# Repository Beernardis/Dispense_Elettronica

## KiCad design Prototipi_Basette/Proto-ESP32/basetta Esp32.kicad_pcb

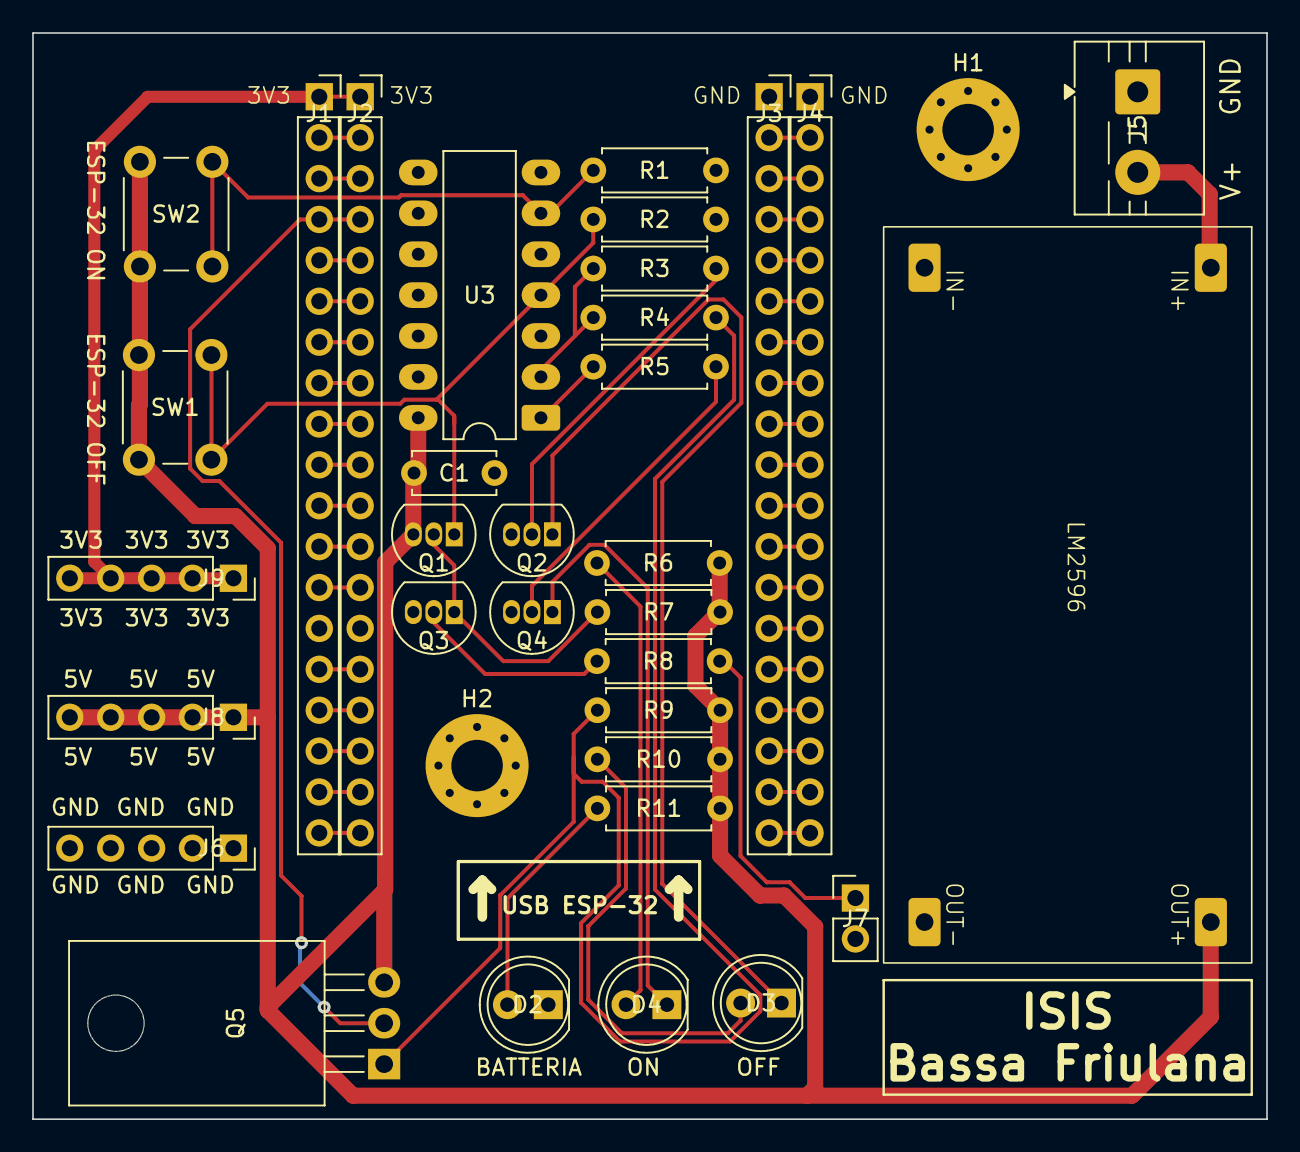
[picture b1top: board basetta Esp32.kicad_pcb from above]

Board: 2 copper layers, 76.6 x 67.5 mm, 35 parts (0 on the bottom side), 54 nets.

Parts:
C1: 100n; C_Disc_D5.0mm_W2.5mm_P5.00mm
D2: LED; LED_D5.0mm
D3: ESP32 OFF; LED_D5.0mm
D4: ESP32 ON; LED_D5.0mm
H1, H2: MountingHole_Pad; MountingHole_3.2mm_M3_Pad_Via
J1, J2, J3, J4: Conn_01x19; PinSocket_1x19_P2.54mm_Vertical
J5: Screw_Terminal_01x02; TerminalBlock_MaiXu_MX126-5.0-02P_1x02_P5.00mm
J6, J8, J9: Conn_01x05; PinSocket_1x05_P2.54mm_Vertical
J7: Conn_01x02; PinHeader_1x02_P2.54mm_Vertical
LM2596: LM2596 - IC
Q1: BC557; TO-92_Inline
Q2, Q3, Q4: BC547; TO-92_Inline
Q5: IRF9540N; TO-220-3_Horizontal_TabDown
R1, R2, R9: 10k; R_Axial_DIN0207_L6.3mm_D2.5mm_P7.62mm_Horizontal
R3, R5: 4.7 k; R_Axial_DIN0207_L6.3mm_D2.5mm_P7.62mm_Horizontal
R4, R6, R10: 470; R_Axial_DIN0207_L6.3mm_D2.5mm_P7.62mm_Horizontal
R7: R; R_Axial_DIN0207_L6.3mm_D2.5mm_P7.62mm_Horizontal
R8: 2.2k; R_Axial_DIN0207_L6.3mm_D2.5mm_P7.62mm_Horizontal
R11: 1k; R_Axial_DIN0207_L6.3mm_D2.5mm_P7.62mm_Horizontal
SW1: RESET; SW_PUSH_6mm_H4.3mm
SW2: SET; SW_PUSH_6mm_H4.3mm
U3: 4013; DIP-14_W7.62mm_LongPads

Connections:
+3V3: J1.1, J2.1, J9.1, J9.2, J9.3, J9.4, J9.5
+5V: C1.1, J8.1, J8.2, J8.3, J8.4, J8.5, LM2596.3 (OUT+), Q1.3 (E), Q5.3 (S), R6.1, R7.1, R9.2, R10.1, R11.1, SW1.1, SW2.1, U3.14 (VDD)
ESP-32 POW: J1.4, J2.4, Q5.2 (D)
GND: C1.2, D2.1 (K), H1.1 (1_1), H2.1 (1_1), J1.14, J2.14, J3.1, J4.1, J5.1, J6.1, J6.2, J6.3, J6.4, J6.5, J7.2, LM2596.2 (IN-), LM2596.4 (OUT-), Q2.3 (E), Q3.3 (E), Q4.3 (E), R1.2, R2.2, U3.3 (C), U3.5 (D), U3.7 (VSS), U3.8 (S), U3.9 (D), U3.10 (R), U3.11 (C)
unnamed: D2.2 (A), R11.2
unnamed: D3.2 (A), R10.2
unnamed: D3.1 (K), Q2.1 (C)
unnamed: D4.2 (A), R6.2
unnamed: D4.1 (K), Q4.1 (C)
unnamed: J1.2, J2.2
unnamed: J1.3, J2.3
unnamed: J1.5, J2.5
unnamed: J1.6, J2.6
unnamed: J1.7, J2.7
unnamed: J1.8, J2.8
unnamed: J1.9, J2.9
unnamed: J1.10, J2.10
unnamed: J1.11, J2.11
unnamed: J1.12, J2.12
unnamed: J1.13, J2.13
unnamed: J1.15, J2.15
unnamed: J1.16, J2.16
unnamed: J1.17, J2.17
unnamed: J1.18, J2.18
unnamed: J1.19, J2.19
unnamed: J3.2, J4.2
unnamed: J3.3, J4.3
unnamed: J3.4, J4.4
unnamed: J3.5, J4.5
unnamed: J3.6, J4.6
unnamed: J3.7, J4.7
unnamed: J3.8, J4.8
unnamed: J3.9, J4.9
unnamed: J3.10, J4.10
unnamed: J3.11, J4.11
unnamed: J3.12, J4.12
unnamed: J3.13, J4.13
unnamed: J3.14, J4.14
unnamed: J3.15, J4.15
unnamed: J3.16, J4.16
unnamed: J3.17, J4.17
unnamed: J3.18, J4.18
unnamed: J3.19, J4.19
unnamed: J7.1, R8.1
unnamed: Q1.2 (B), Q3.1 (C), R7.2
unnamed: Q2.2 (B), R3.2
unnamed: Q3.2 (B), R8.2
unnamed: Q4.2 (B), R5.2
unnamed: Q5.1 (G), R4.2, R9.1
unnamed: R5.1, U3.1 (Q)
unnamed: R1.1, SW2.2, U3.6 (S)
SIGN_ESP32: R3.1, R4.1, U3.2 (~Q)
Suicide: Q1.1 (C), R2.1, SW1.2, U3.4 (R)
V_in_Batterie: J5.2, LM2596.1 (IN+)

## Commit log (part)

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2026-03-15 Primo commit
2026-03-16 Add Sarrus diagram and adjust TikZ config
    Introduce a TikZ illustration of Sarrus' rule in Gauss_Jordan.tex and clarify the explanatory text (explicitly mention the 3x5 layout and diagonal conventions). Reformat determinant calculations for 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
2026-03-17 Add Metodo Correnti di Maglia chapter & exercises
    Introduce the 'Metodo delle Correnti di Maglia' content: add CorrentiMaglia.tex (chapter) and a comprehensive Esercizi.tex with exercise sets and worked solutions (Cramer's rule and Gauss–Jordan). Re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
2026-03-17 Restructure methods and add DC & Sallen-Key drafts
    Reorganize and expand course material: rename MetodoPotenzialeNodi to Metodi_AC (capitolo1/2 and main.tex). Add a new Metodi_DC module with chapters for Correnti_Maglia, Potenziale_Nodi, PDSDE (super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
2026-03-18 Rename Metodi_DC files and add mesh chapter
    Reorganize MetodiRisolutiviReti/Metodi_DC: add a new numbered chapter file 1_Correnti_Maglia.tex (detailed mesh-current method with circuit example), delete the old Correnti_Maglia.tex, and rename ex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
2026-03-18 Revise mesh-current example and add procedure
    Reworks the 'correnti di maglia' example: minor wording cleanup in the mesh-current definition, adds a systematic step-by-step procedure to derive mesh equations, and introduces a more detailed circu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
2026-03-18 Enhance mesh-current method section
    Add detailed exposition of the mesh-current (correnti di maglia) method: introductory paragraph on its purpose, requirements for planar circuits, and identification of independent meshes. Clarify Eul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
2026-03-18 Refine mesh-current example and add matrix section
    Improve formatting and pedagogy of the mesh-current example: enlarge the example subsection title, add horizontal rules for visual separation, and tweak enumeration labels (rename steps and make the 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
2026-03-19 Aggiungi vettore corrente di maglia e vettore b
    Aggiunte le sottosezioni che definiscono il vettore incognita I e il vettore dei termini noti b, con convenzione sui segni per i generatori. Inseriti esempi espliciti di I e b, la forma matriciale es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
2026-03-19 Gestione generatori di corrente nel metodo maglie
    Aggiunta una sezione che tratta il problema dei generatori di corrente nel metodo delle correnti di maglia. Introduce la procedura: mantenere le correnti di maglia come incognite, aggiungere variabil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
2026-03-19 Terminato Correnti di maglia
    Non compila, probabilmente problemi di include/input
2026-03-20 Update mesh-current chapter: edits & fixes
    Replace \include with \input and perform multiple content and formatting refinements in the mesh-current (correnti di maglia) chapter. Expanded and clarified the procedural steps (LKT, Ohm, matrix fo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
2026-03-20 Restructure DC methods and add node method
    Reorganize Metodi_DC layout and add the Metodo del potenziale ai nodi chapter. Several files were moved/renamed into per-chapter subfolders (3,4,5,6 renamed to their /<n>_main.tex paths). Removed obs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
2026-03-21 Enhance node-potential docs and circuit macros
    Refine documentation and diagram macros for the nodal-potential method:
    - Risoluzione_E.tex: rename section from "Procedura di risoluzione" to "Problema del generatore di tensione".
    - Risoluzione_J.tex: replace placeholder with a full step-by-step nodal-potential procedure, including theory, example, KCL equations, Ohm-law substitutions and matrix form; adds explanatory figures 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
    - cenni_teorici.tex: small wording/formatting fixes around Ohm's law and conductances.
    - Circuiti.tex: overhaul the \CircuitoPotenzialeNodi macro to draw explicit current/voltage sources, support grounded and non-grounded variants, i
2026-03-22 Metodo dei nodi: generatori di tensione
    Aggiunge una sezione completa che spiega come gestire generatori di tensione ideali nel metodo dei potenziali ai nodi: vengono introdotte le correnti dei generatori come incognite, le equazioni di vi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
2026-03-23 Fix nodal equations and correct source labels
    Correct KCL equations and expand the nodal analysis in Resoluzione_E.tex: clarify current directions for voltage sources, rename nodes consistently (A, C, D), rewrite KCLs, apply Ohm's law using cond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
2026-03-23 Include voltage source currents in node KCL
    Refactor the node KCL/Ohm section to explicitly include the unknown currents of voltage sources (I_{E1}, I_{E2}) and update the corresponding KCL equations and Ohm-law substitutions. Replace itemize 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
2026-03-24 Fix voltage-source constraints and matrix signs
    Clarify and correct the voltage-source connections and their algebraic constraints: E1 is now defined between D and C and E2 between A and B (previously C–D and B–C). The source equations were rewrit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
2026-03-27 Refactor LaTeX: move documentclass, adjust macros
    Centralize document class and tidy LaTeX sources: moved \documentclass from MetodiRisolutiviReti/Metodi_DC/_main.tex into config/config.tex (now \documentclass[a4paper, 11pt]{book}). Update header to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
2026-03-27 Add LaTeX main and update config
    Create a top-level LaTeX entry point (LaTeX/main.tex) with title, TOC and several chapter placeholders. Remove the duplicate \documentclass from config/config.tex and centralize package setup by addi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
2026-03-29 Use identity block for voltage sources and update matrix
    Replace the bottom-right zero block in the augmented nodal matrix with an identity to represent independent voltage-source currents. Update the E and I block definitions and the expanded 5x5 system r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
2026-03-31 Fix node labels and sign in nodal equations
    Rename ZoomNodo references for nodes A, C and D to A_1, C_1, D_1 and add matching drawing cases in Circuiti.tex for the new zoom identifiers. Correct the sign of the J_2 term in node D's KCL and upda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
2026-04-01 Add Arduino LED tutorial (Italian LaTeX)
    Add new LaTeX file Arduino/main.tex containing a comprehensive Italian chapter on LEDs. Covers physical principles, polarity, electrical parameters, resistor calculation, breadboard wiring, PWM, and 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
2026-04-01 Extract LED chapter to Arduino/LED.tex
    Move the LED chapter out of main.tex into a new Arduino/LED.tex to modularize the documentation. Added accompanying images (Arduino/img/Circuito_LED_Generatore.png and Arduino/img/Struttura_fisica_LE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
2026-04-01 Add LED PWM example and formatting tweaks
    Introduce a new Arduino example (Esempio 2) demonstrating PWM-driven LED brightness using analogWrite on PIN_LED = 13 with two duty cycles (50 and 200) and 1s delays. Also add horizontal rules around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
2026-04-03 Add LED circuit images and examples
    Insert two new circuit images and a side-by-side figure into Arduino/LED.tex to illustrate a 5V test circuit and an Arduino-driven LED circuit. Update explanatory text to reference the new figures, u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
2026-04-03 Update LED chapter: formatting, examples, RGB
    Refactor LED chapter: convert many \subsection to unnumbered \subsection*, adjust figure layout (minipage widths and image sizing) and captions, and tweak math/notation for clarity. Add a new "LED RG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
2026-04-04 Update LED chapter: PWM, RGB, examples
    Revise LED chapter: refactor sections and examples for clarity and PWM/RGB usage. Made subsection unnumbered, adjusted image sizing, replaced circuitikz diagram with raster image, and updated recomme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
2026-04-08 Add Arduino board sheet and pinout image
    Add new Schede_Arduino.tex and Arduino_uno_PinOut.jpg to provide an Arduino board sheet/pinout reference, and update main.tex to include the new Schede_Arduino file so the pinout is included in the c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
2026-04-08 Add Arduino chapter file
    Add new LaTeX chapter file Arduino/Schede_Arduino.tex containing a chapter header '\chapter{Scheda Arduino}' as a placeholder for Arduino content.
2026-04-09 Expand Arduino chapter with intro and pin details
    Replace the old 'Scheda Arduino' chapter with a much more detailed 'Introduzione ad Arduino'. Adds structured sections on the Arduino Uno overview, power (USB, DC jack, Vin), onboard linear regulator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
2026-04-28 Add Pulsante chapter and button images
    Add a new Arduino chapter (pulsante.tex) documenting push-button usage: structure, pull-up/pull-down wiring, internal pull-up, debouncing (software delay and Bounce2), press-duration measurement, and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
2026-05-01 Document serial TX/RX and add Bounce2 example
    Adds a new detailed section about serial communication (USART/UART) to Schede_Arduino.tex covering pins 0/1 (RX/TX), baud rate, USB-serial converter (ATmega16U2), TX/RX LEDs and upload-time interfere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
2026-05-11 Add ESP32 prototype PCB and backup files
    Import KiCad project for basetta Esp32 including basetta Esp32.kicad_pcb, .kicad_sch, .kicad_pro, .kicad_prl and fp-info-cache, plus multiple timestamped backup ZIPs under Prototipi Basette/Proto-ESP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
2026-05-12 Add LM2596 symbol/footprint and update PCB
    Add LM2596 footprint and symbol libraries, update project schematic and PCB files, and refresh project metadata. Includes new Library.pretty/LM2596 - IC footprint, Simboli_Progetto.* symbol library f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
2026-05-12 Update ESP32 board files and docs
    Add compiled Arduino/main.pdf and simplify Arduino/pulsante.tex (remove blocking debouncing example and tidy Bounce2 section). Add several timestamped basetta Esp32 backup ZIPs. Large KiCad changes t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
2026-05-13 Update KiCad PCB to newer format and footprints
    Upgrade basetta Esp32.kicad_pcb to a newer pcbnew/generator version and apply footprint/pad updates. Changes include generator/version bump, expanded setup entries (tenting/covering/plugging), conver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
2026-05-13 Modifica PCB - Parallelo Suicide
    Aggiunto comando suicide da ESP32
2026-05-13 Add Primo Circuito KiCad project; update ESP32 PCB
    Add a new KiCad project "Primo Circuito KiCad": schematic (.kicad_sch), board file (.kicad_pcb), project/settings (.kicad_pro, .kicad_prl) and a PDF export (BERNARDIS.pdf). The schematic contains a s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
2026-05-13 Renamed folders
2026-05-14 Versione Stabile
    Versione stabile con GND a piste, senza diodo nel suicide
2026-05-14 Update KiCad PCB footprint positions and metadata
    Adjust PCB layout: moved and rotated multiple footprints (resistors, DIP ICs, TO-92/TO-220 transistors, push button, switch, LM2596, etc.), corrected pad orientations (added/changed pad rotation angl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
2026-05-14 Add STEP models; update ESP32 PCB & project
    Add 3D STEP models for DG350-3.96-02P-12-00AH and LM2596 under Prototipi_Basette/Proto-ESP32, and update basetta Esp32.kicad_pcb and basetta Esp32.kicad_prl to incorporate/reflect these parts. Also a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
2026-05-15 Adjust PCB footprints, pads and routing
    Move and reorient multiple footprints and update PCB geometry/metadata for the Proto-ESP32 layout. Changes include repositioning several resistors, TO-92 transistors, LEDs and a pin header; adding/ad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
2026-05-15 Update MOSFET footprint, nets and refs
    Modify PCB to replace a TO-92 footprint with a TO-220 horizontal power MOSFET (IRF9540N) and update related component properties, 3D model and datasheet. Fix pad nets (Q3-G -> Q6-G), adjust component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
2026-05-15 Add mounting holes and tidy PCB footprints
    Added two M3 mounting-hole footprints and multiple thru-hole pads (GND connected). Cleaned up many footprints by hiding F.Fab value/reference texts, removing redundant fp_text user elements, and adju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
2026-05-15 Add ITTCV-TDP-04 ESP32 board variant
    Add new KiCad project files for the basetta Esp32-ITTCV-TDP-04 variant (basetta Esp32-ITTCV-TDP-04.kicad_pcb, .kicad_prl, .kicad_sch). Also update the main basetta Esp32 files (basetta Esp32.kicad_pc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
2026-05-15 Update ESP32 prototype files and add Gerbers
    Remove obsolete Basetta_ESP32.zip and ITTCV-TDP-04 KiCad variant files; apply updates to the main KiCad project files (basetta Esp32.kicad_pcb, .kicad_prl, .kicad_pro, .kicad_sch). Add Gerber.zip wit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
2026-05-15 Remove app.freerouting.kicad-plugin_v2.2.0.zip
    Delete the binary zip file app.freerouting.kicad-plugin_v2.2.0.zip from the Prototipi_Basette directory. Removes the bundled freerouting KiCad plugin archive (binary) from the repository to clean up 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
